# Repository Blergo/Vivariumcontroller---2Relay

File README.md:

**Slave with two 10A 250V relays for the Vivarium Controller project - For more information please see "VivariumController---Master" Repository.**

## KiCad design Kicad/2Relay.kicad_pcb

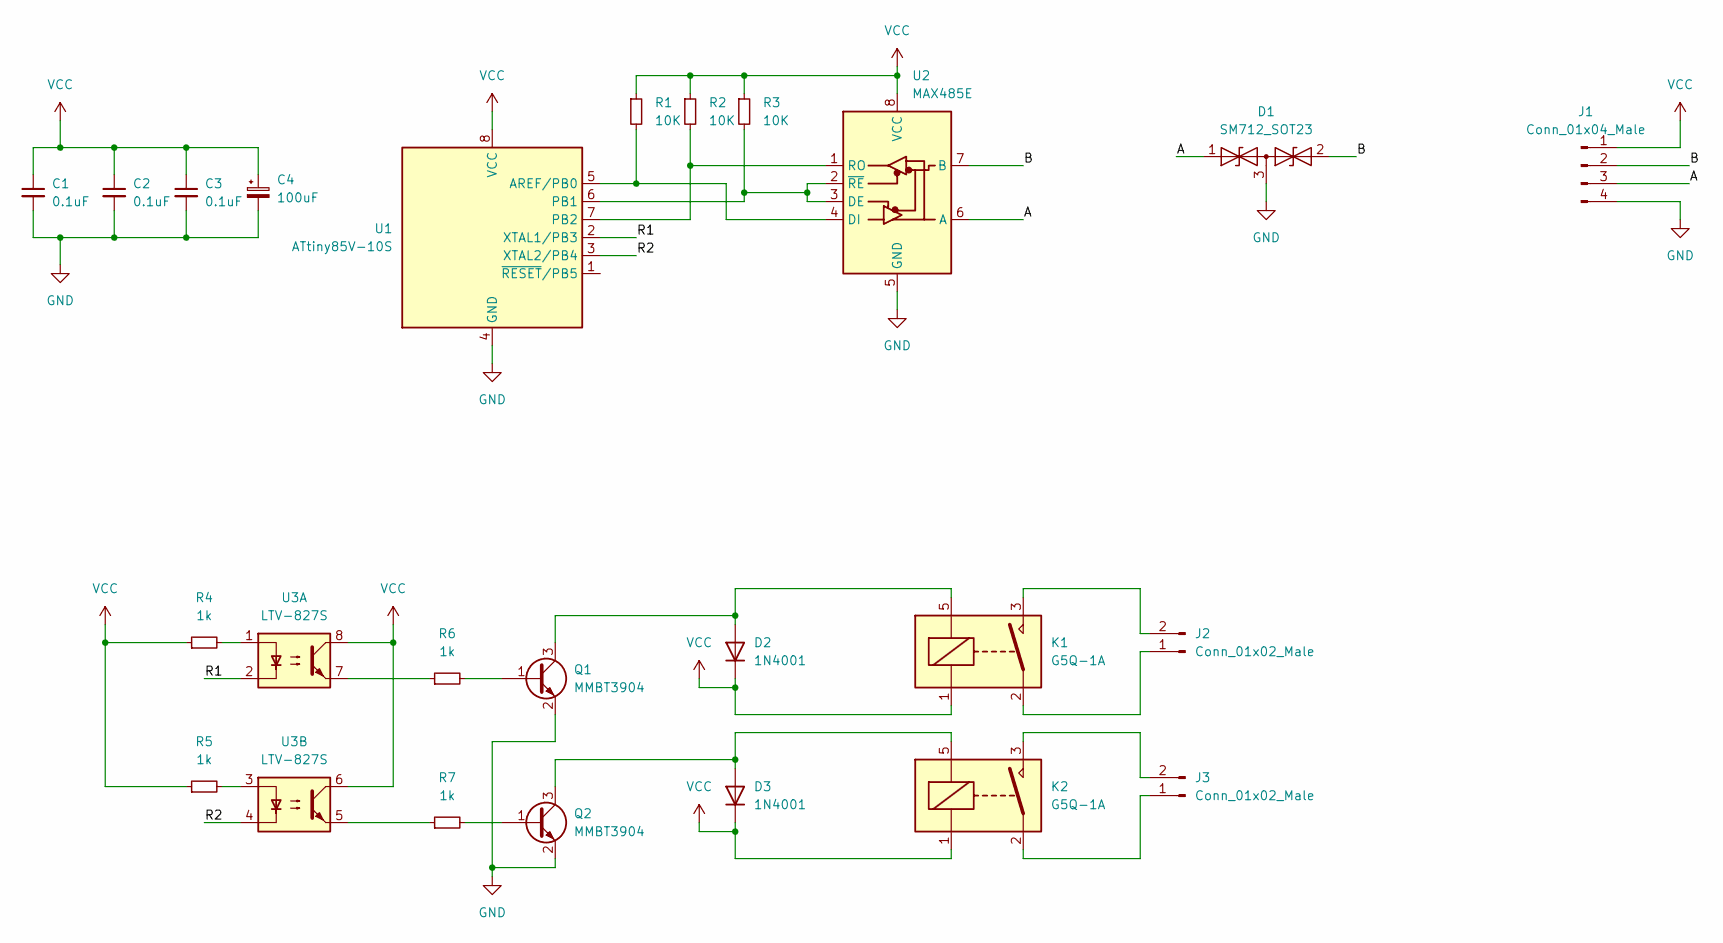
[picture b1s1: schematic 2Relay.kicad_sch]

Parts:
C1, C2, C3: 0.1uF; C_0805_2012Metric
C4: 100uF; CP_Radial_D6.3mm_P2.50mm
D1: SM712_SOT23; SOT-23
D2, D3: 1N4001; D_SMA
J1: Conn_01x04_Male; PinHeader_1x04_P1.27mm_Vertical
J2, J3: Conn_01x02_Male; SolderWire-2.5sqmm_1x02_P7.2mm_D2.4mm_OD3.6mm
K1, K2: G5Q-1A; Relay_SPST_Omron-G5Q-1A
Q1, Q2: MMBT3904; SOT-23
R1, R2, R3: 10K; R_0603_1608Metric
R4, R5, R6, R7: 1k; R_0603_1608Metric
U1: ATtiny85V-10S; SOIC-8W_5.3x5.3mm_P1.27mm
U2: MAX485E; SOIC-8_3.9x4.9mm_P1.27mm
U3: LTV-827S; SMDIP-8_W9.53mm

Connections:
/A: D1.1 (A1), J1.3, U2.6 (A)
/B: D1.2 (A2), J1.2, U2.7 (B)
/R1: U1.2 (XTAL1/PB3), U3.2
/R2: U1.3 (XTAL2/PB4), U3.4
GND: C1.2, C2.2, C3.2, C4.2, D1.3 (common), J1.4, Q1.2 (E), Q2.2 (E), U1.4 (GND), U2.5 (GND)
unnamed: J2.1, K1.2
unnamed: J2.2, K1.3
unnamed: J3.1, K2.2
unnamed: J3.2, K2.3
unnamed: D2.2 (A), K1.5, Q1.3 (C)
unnamed: D3.2 (A), K2.5, Q2.3 (C)
unnamed: R1.2, U1.5 (AREF/PB0), U2.4 (DI)
unnamed: R2.2, U1.7 (PB2), U2.1 (RO)
unnamed: R3.2, U1.6 (PB1), U2.2 (~RE), U2.3 (DE)
unnamed: Q1.1 (B), R6.2
unnamed: Q2.1 (B), R7.2
unnamed: R4.2, U3.1
unnamed: R5.2, U3.3
unnamed: R7.1, U3.5
unnamed: R6.1, U3.7
VCC: C1.1, C2.1, C3.1, C4.1, D2.1 (K), D3.1 (K), J1.1, K1.1, K2.1, R1.1, R2.1, R3.1, R4.1, R5.1, U1.8 (VCC), U2.8 (VCC), U3.6, U3.8

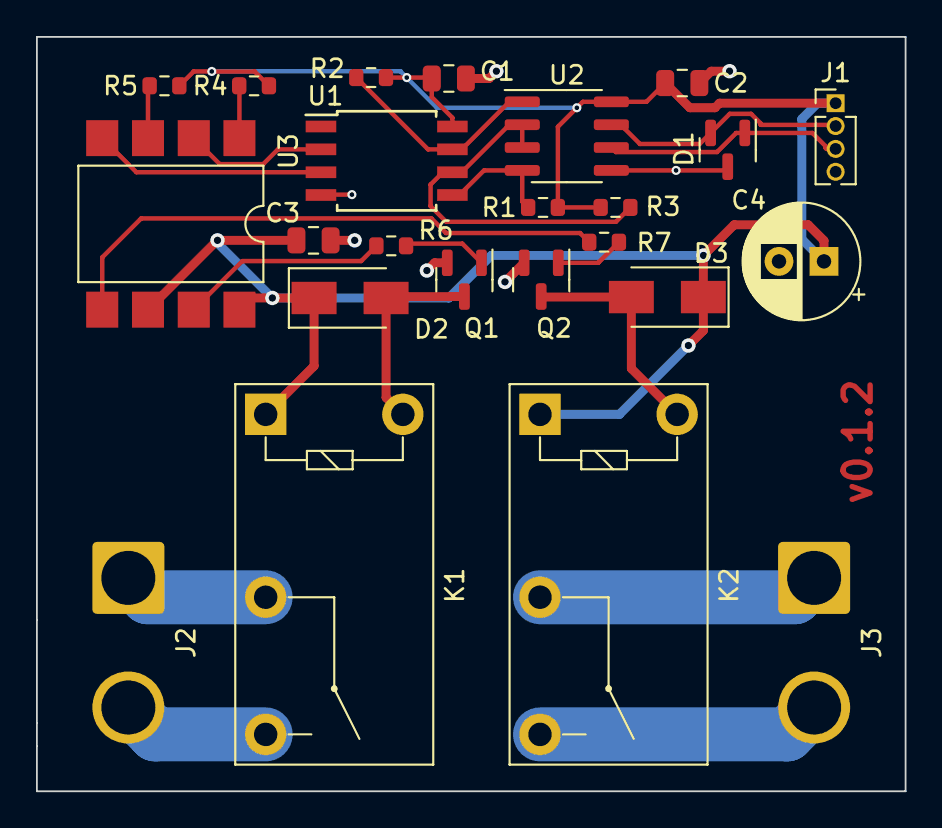
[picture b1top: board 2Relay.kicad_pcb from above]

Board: 2 copper layers, 48.3 x 41.9 mm, 24 parts (0 on the bottom side), 21 nets.

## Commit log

2021-12-30 Initial Code
2021-12-30 removed a delay
2021-12-30 Pin setup
2021-12-30 relay control code
2022-01-01 Changed slave assignment
2022-01-01 Changes to enable isp programming
2022-01-08 added PCB files.
2022-01-09 Updated PCB to v0.1.2
